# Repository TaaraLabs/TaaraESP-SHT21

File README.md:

TaaraESP SHT21
==============

[WebSite](https://taaralabs.eu/es1)

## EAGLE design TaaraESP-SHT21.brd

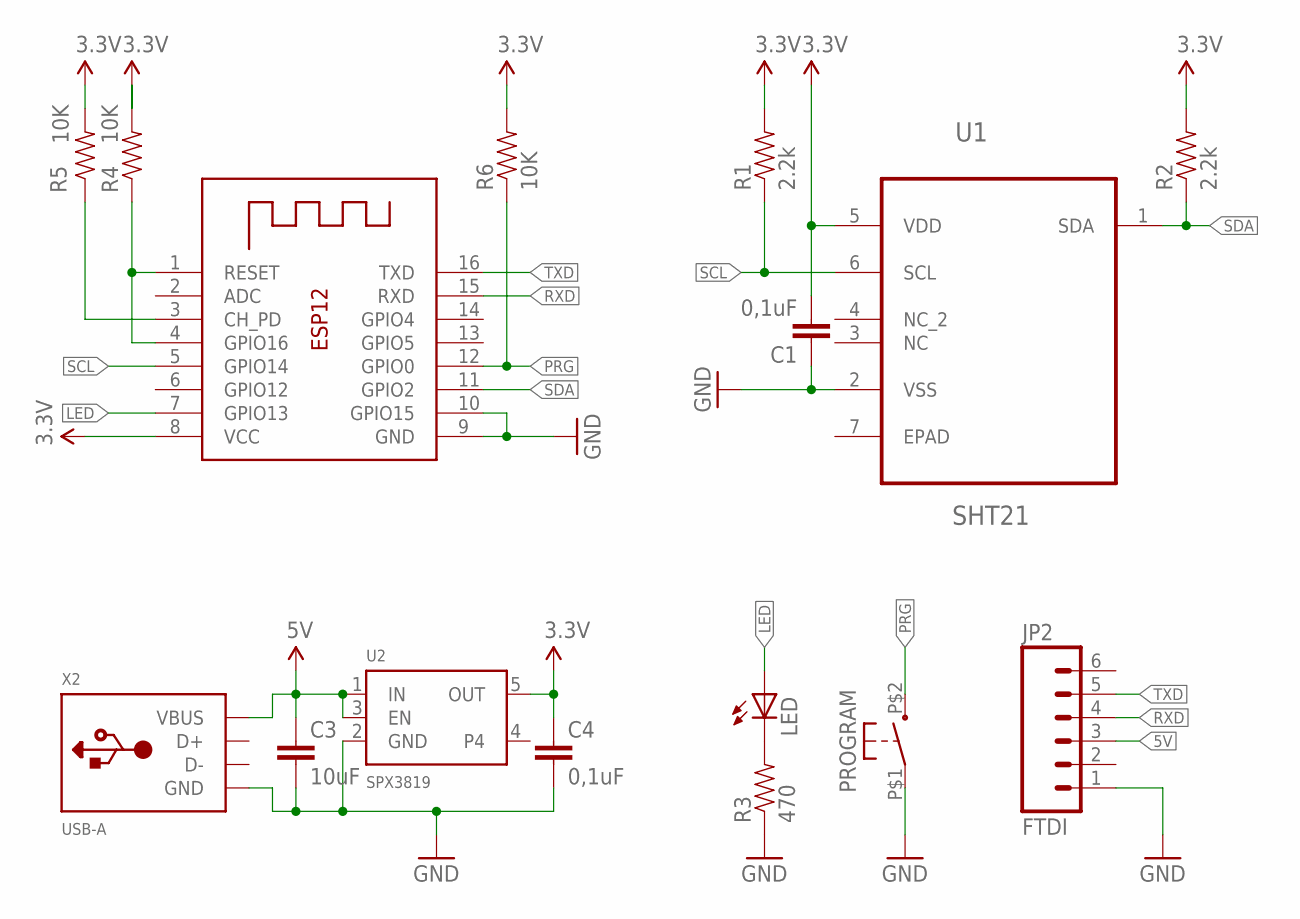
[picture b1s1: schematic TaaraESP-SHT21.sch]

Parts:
C1, C4: 0,1uF; 0603-CAP
C3: 10uF; 0603-CAP
JP2: FTDI; 1X06-SIP_LOCK
LED: LEDCHIPLED_0603; CHIPLED_0603
PROGRAM: OMRON_B3U-1000_TACT_SW; BC3-1000
R1, R2: 2.2k; 0603-RES
R3: 470; 0603-RES
R4, R5, R6: 10K; 0603-RES
U1: SHT21; DFN300X300X110-7N
U2: SPX3819; SOT23-5
X1: ESP-12
X2: USB-A; MOLEX_480371000

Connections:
3.3V: C1.2, C4.1, R1.2, R2.2, R4.2, R5.2, R6.2, U1.5 (VDD), U2.5 (OUT), X1.8 (VCC)
5V: C3.1, JP2.3, U2.1 (IN), U2.3 (EN), X2.1 (VBUS)
GND: C1.1, C3.2, C4.2, JP2.1, PROGRAM.P$1 (1), R3.1, U1.2 (VSS), U2.2 (GND), X1.9 (GND), X1.10 (GPIO15), X2.4 (GND)
LED: LED.A, X1.7 (GPIO13)
unnamed: LED.C, R3.2
unnamed: R4.1, X1.1 (RESET), X1.4 (GPIO16)
unnamed: R5.1, X1.3 (CH_PD)
PRG: PROGRAM.P$2 (3), R6.1, X1.12 (GPIO0)
RXD: JP2.4, X1.15 (RXD)
SCL: R1.1, U1.6 (SCL), X1.5 (GPIO14)
SDA: R2.1, U1.1 (SDA), X1.11 (GPIO2)
TXD: JP2.5, X1.16 (TXD)

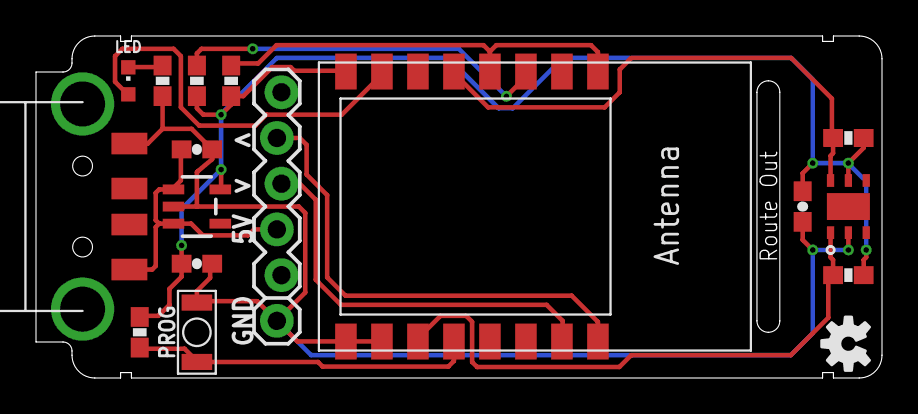
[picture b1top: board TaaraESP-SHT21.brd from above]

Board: 2 copper layers, 47.0 x 19.0 mm, 18 parts (1 on the bottom side), 12 nets.

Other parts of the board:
U$1, U$5: OSHW-LOGO-S

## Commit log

2015-10-13 :lollipop: Added .gitattributes & .gitignore files
2015-10-13 Initial upload

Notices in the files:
parts and their libraries:
microbuilder: This work is placed in the public domain, and may be freely used for commercial and non-commercial work with the following conditions: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
SparkFun-Aesthetics: Licensing: CC v3.0 Share-Alike You are welcome to use this library for commercial purposes.
